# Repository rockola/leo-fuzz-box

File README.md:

# leo-fuzz-box

Fuzz Box by Anthony Leo from Popular Electronics, Feb. 1968 

* v0.1: initial import, unverified
* v0.2: tighter layout, Gerbers sent to Oshpark
* v0.3: C2 moved to correct spot

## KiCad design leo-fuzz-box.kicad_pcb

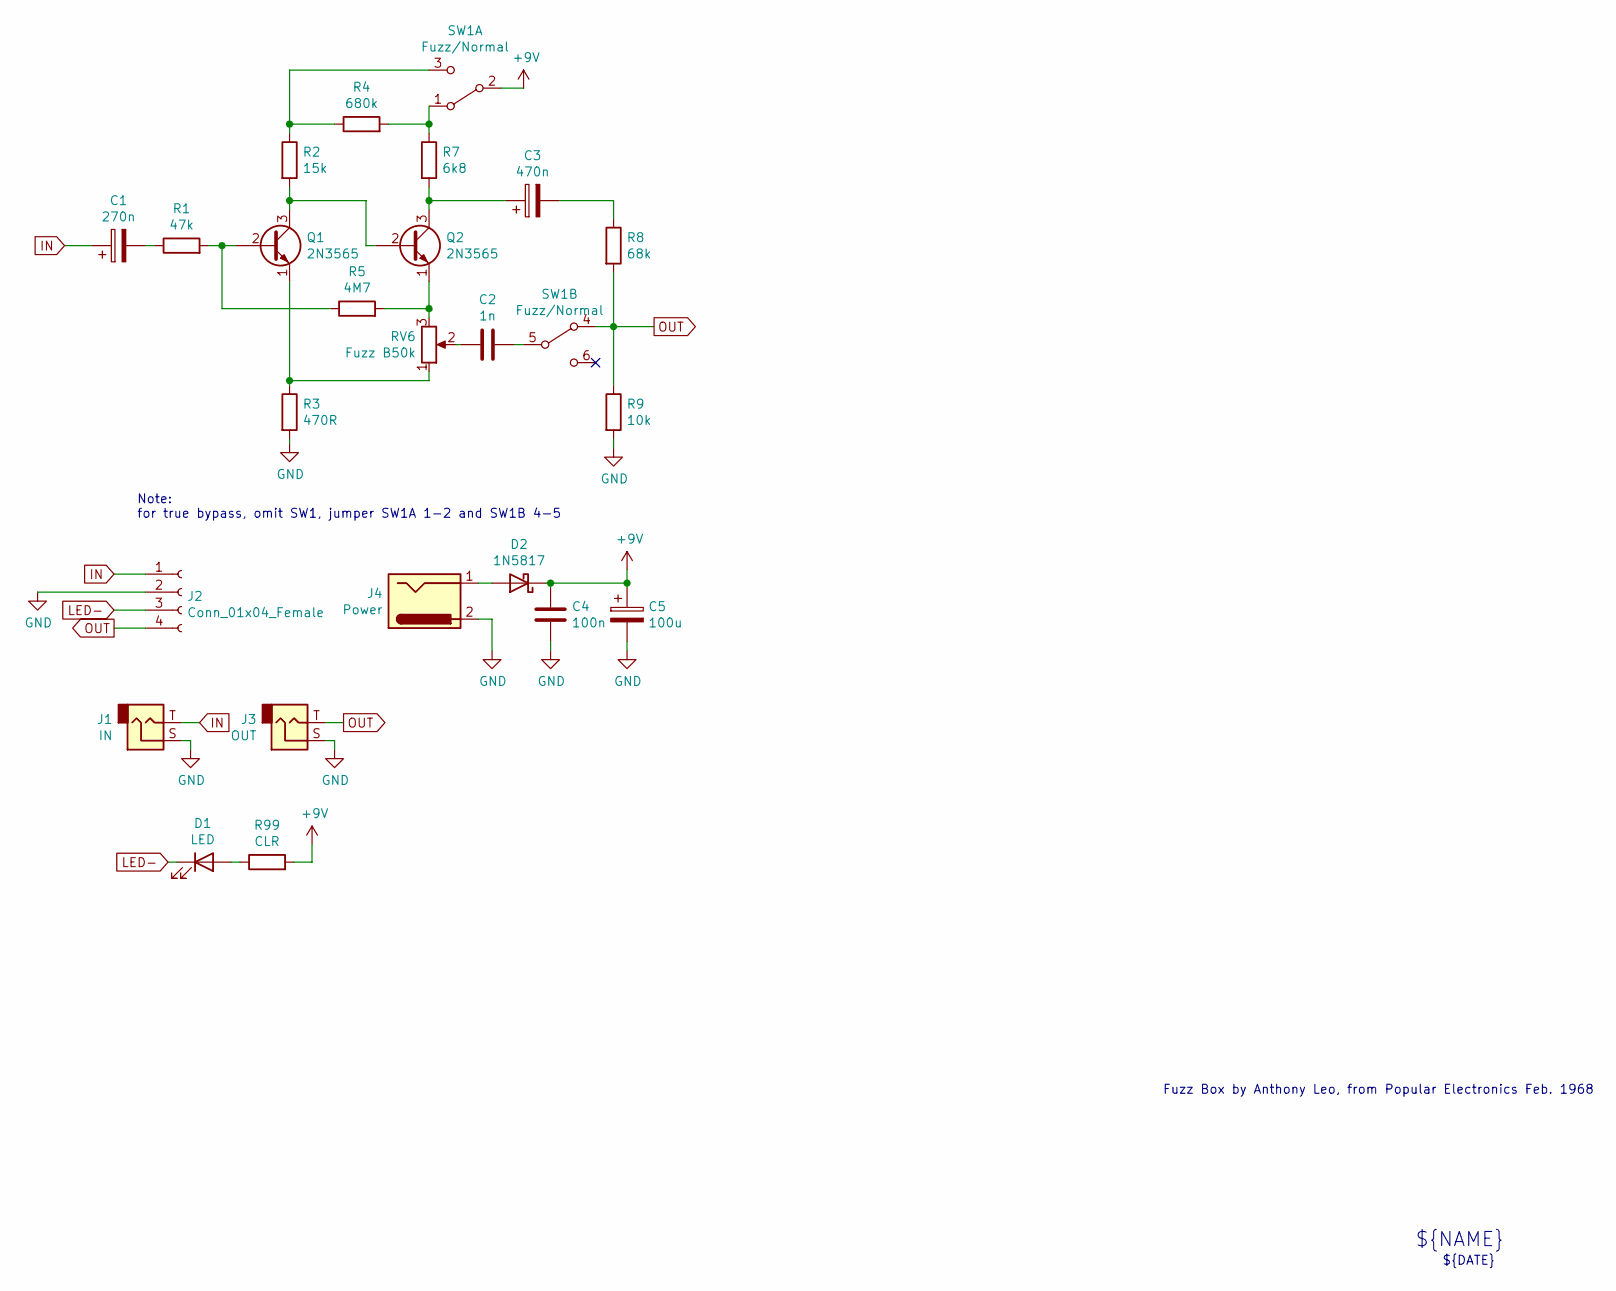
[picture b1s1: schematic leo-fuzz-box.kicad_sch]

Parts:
C1: 270n; C_Box_7.2_2.5
C2: 1n; C_Box_7.2_2.5
C3: 470n; C_Box_7.2_2.5
C4: 100n; C_Box_7.2_2.5
C5: 100u; CP_D5.0_P2.50
D1: LED; LED.3mm
D2: 1N5817; D_DO-41_SOD81_P10.16mm_Horizontal
J1: IN; 2PADS_TipSleeve
J2: Conn_01x04_Female; Stomp_4pin
J3: OUT; 2PADS_TipSleeve
J4: Power; Power_Header_2pin
Q1, Q2: 2N3565; TO92
R1: 47k; R_DIN0207
R2: 15k; R_DIN0207
R3: 470R; R_DIN0207
R4: 680k; R_DIN0207
R5: 4M7; R_DIN0207
R7: 6k8; R_DIN0207
R8: 68k; R_DIN0207
R9: 10k; R_DIN0207
R99: CLR; R_DIN0207
RV6: Fuzz B50k; 16MM_B.MOUNT
SW1: Fuzz/Normal; DPDT.WIRE

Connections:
+9V: C4.1, C5.1, D2.1 (K), R99.2, SW1.2 (B)
GND: C4.2, C5.2, J1.S, J2.2, J3.S, J4.2, R3.2, R9.2
IN: C1.1, J1.T, J2.1
LED-: D1.1 (K), J2.3
unnamed: C1.2, R1.1
unnamed: C2.1, RV6.2
unnamed: C2.2, SW1.5 (B)
unnamed: C3.1, Q2.3 (C), R7.2
unnamed: C3.2, R8.1
unnamed: D1.2 (A), R99.1
unnamed: D2.2 (A), J4.1
unnamed: Q1.1 (E), R3.1, RV6.1
unnamed: Q1.2 (B), R1.2, R5.1
unnamed: Q1.3 (C), Q2.2 (B), R2.2
unnamed: Q2.1 (E), R5.2, RV6.3
unnamed: R2.1, R4.1, SW1.3 (C)
unnamed: R4.2, R7.1, SW1.1 (A)
OUT: J2.4, J3.T, R8.2, R9.1, SW1.4 (A)

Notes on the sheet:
${REVISION}
${NAME}
${DATE}
Note: for true bypass, omit SW1, jumper SW1A 1-2 and SW1B 4-5
Fuzz Box by Anthony Leo, from Popular Electronics Feb. 1968

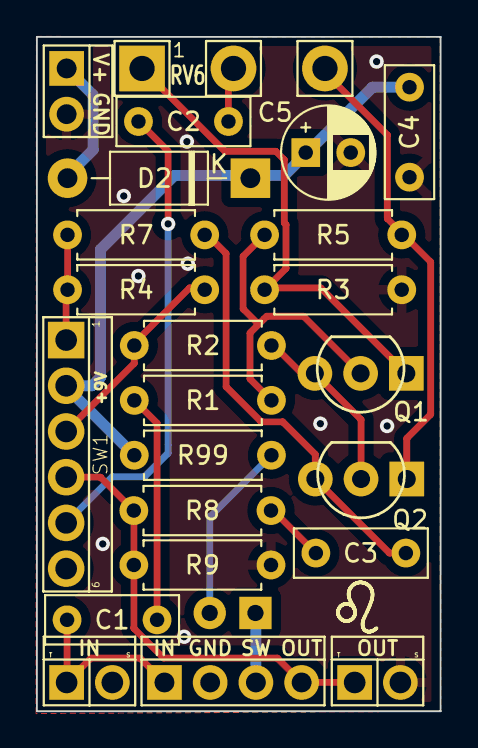
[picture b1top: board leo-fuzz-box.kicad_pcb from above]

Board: 2 copper layers, 22.4 x 37.5 mm, 24 parts (1 on the bottom side), 18 nets.

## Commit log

2020-08-19 initial version
2020-08-19 added power protection, finished first version of pcb layout
2020-08-19 initial gerbers
2020-08-19 oshpark preview
2020-08-19 v0.1 schematic png
2020-08-19 packed tighter but functionally the same
2020-08-19 schematic preview
2020-08-20 v0.2: tighter layout, Gerbers sent to Oshpark
2020-08-24 v0.3: C2 goes between pot and switch
2022-01-11 updated to KiCad 6.0
